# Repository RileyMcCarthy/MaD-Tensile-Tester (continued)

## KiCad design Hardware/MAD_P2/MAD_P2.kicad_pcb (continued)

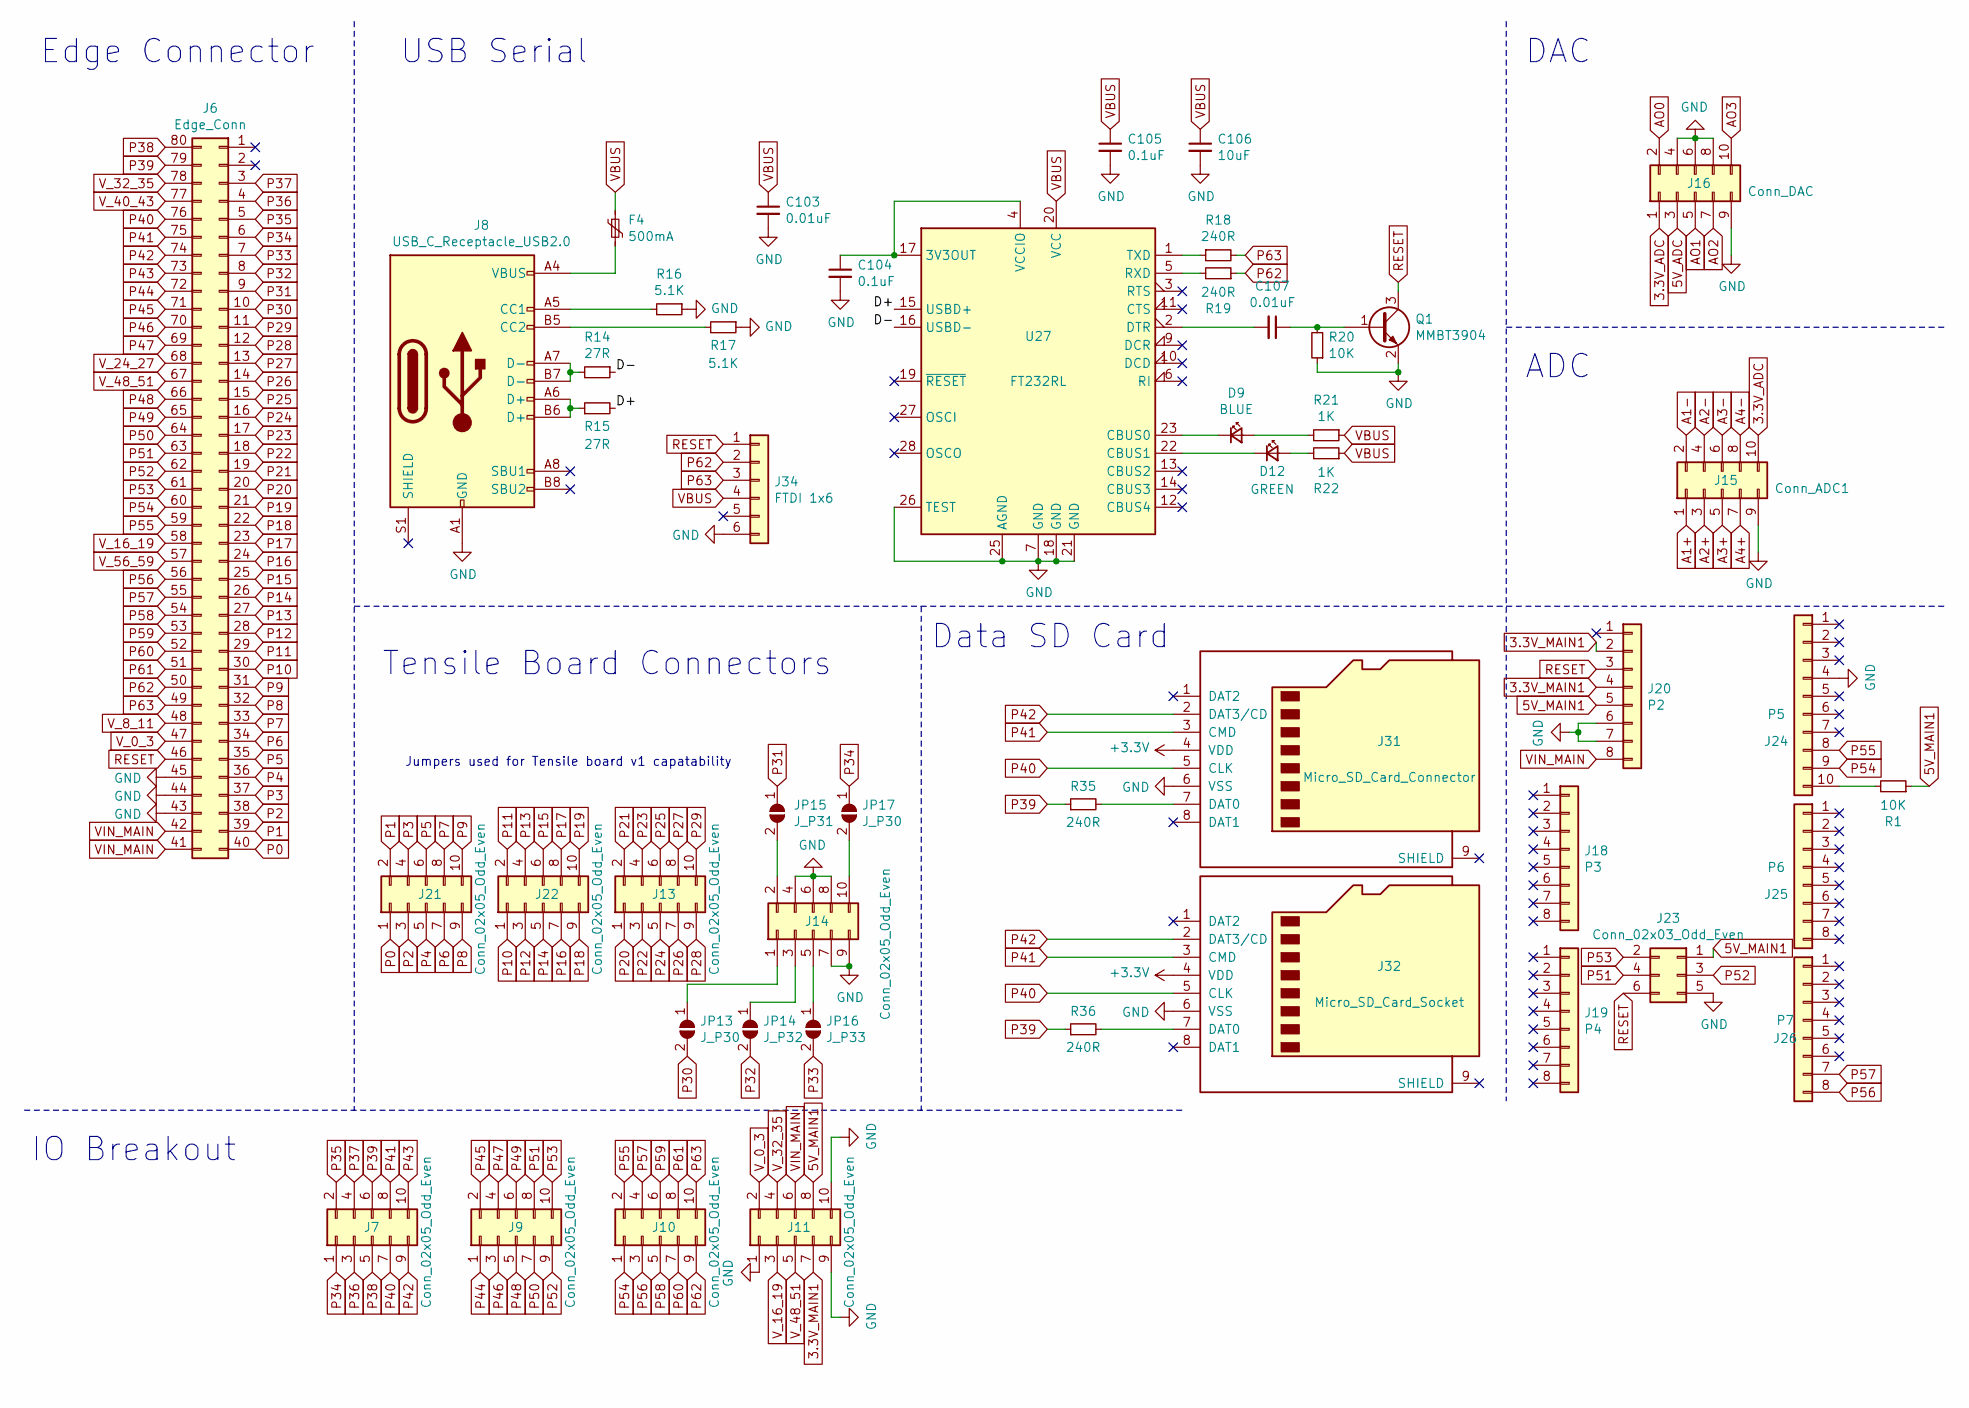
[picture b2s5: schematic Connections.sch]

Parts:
C103, C107: 0.01uF; C_0603_1608Metric; LCSC C57112
C104, C105: 0.1uF; C_0603_1608Metric; LCSC C14663
C106: 10uF; C_0805_2012Metric; LCSC C15850
D9: BLUE; LED_0603_1608Metric; LCSC C72041
D12: GREEN; LED_0603_1608Metric; LCSC C72043
F4: 500mA; Fuse_0603_1608Metric; LCSC C261937
J6: Edge_Conn; P2_Edge_Conn
J7, J9, J10, J11, J13, J14, J21, J22: Conn_02x05_Odd_Even; IDC-Header_2x05_P2.54mm_Vertical; LCSC C5665
J8: USB_C_Receptacle_USB2.0; USB_C_Receptacle_Palconn_UTC16-G; LCSC C393939
J15: Conn_ADC1; IDC-Header_2x05_P2.54mm_Vertical; DIGIKEY S9169-ND
J16: Conn_DAC; IDC-Header_2x05_P2.54mm_Vertical; DIGIKEY S9169-ND
J18: P3; PinSocket_1x08_P2.54mm_Vertical; LCSC C27438
J19: P4; PinSocket_1x08_P2.54mm_Vertical; LCSC C27438
J20: P2; PinSocket_1x08_P2.54mm_Vertical; LCSC C27438
J23: Conn_02x03_Odd_Even; PinSocket_2x03_P2.54mm_Vertical; LCSC C92272
J24: P5; PinSocket_1x10_P2.54mm_Vertical; LCSC C35445
J25: P6; PinSocket_1x08_P2.54mm_Vertical; LCSC C27438
J26: P7; PinSocket_1x08_P2.54mm_Vertical; LCSC C27438
J31: Micro_SD_Card_Connector; WM26501; DIGIKEY WM26501
J32: Micro_SD_Card_Socket; microSD_HC_Hirose_DM3D-SF; DIGIKEY 732-3820-2-ND
J34: FTDI 1x6; PinHeader_1x06_P2.54mm_Vertical
JP13, JP17: J_P30; SolderJumper-2_P1.3mm_Open_Pad1.0x1.5mm
JP14: J_P32; SolderJumper-2_P1.3mm_Open_Pad1.0x1.5mm
JP15: J_P31; SolderJumper-2_P1.3mm_Open_Pad1.0x1.5mm
JP16: J_P33; SolderJumper-2_P1.3mm_Open_Pad1.0x1.5mm
Q1: MMBT3904; SOT-23; LCSC C20526
R1, R20: 10K; R_0603_1608Metric; LCSC C25804
R14, R15: 27R; R_0603_1608Metric; LCSC C25190
R16, R17: 5.1K; R_0603_1608Metric; LCSC C23186
R18, R19, R35, R36: 240R; R_0603_1608Metric; LCSC C23350
R21, R22: 1K; R_0603_1608Metric; LCSC C21190
U27: FT232RL; SSOP-28_5.3x10.2mm_P0.65mm; LCSC C8690

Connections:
3.3V_ADC: J15.10, J16.1; also elsewhere on the board
3.3V_MAIN1: J11.7, J20.2, J20.4; also elsewhere on the board
5V_ADC: J16.3; also elsewhere on the board
5V_MAIN1: J11.8, J20.5, J23.1, R1.1; also elsewhere on the board
+3V3: J31.4 (VDD), J32.4 (VDD); also elsewhere on the board
/Connections/D+: R15.2, U27.15 (USBD+)
/Connections/D-: R14.1, U27.16 (USBD-)
A1+: J15.1; also elsewhere on the board
A1-: J15.2; also elsewhere on the board
A2+: J15.3; also elsewhere on the board
A2-: J15.4; also elsewhere on the board
A3+: J15.5; also elsewhere on the board
A3-: J15.6; also elsewhere on the board
A4+: J15.7; also elsewhere on the board
A4-: J15.8; also elsewhere on the board
AO0: J16.2; also elsewhere on the board
AO1: J16.5; also elsewhere on the board
AO2: J16.7; also elsewhere on the board
AO3: J16.10; also elsewhere on the board
GND: C103.2, C104.2, C105.2, C106.2, J6.43, J6.44, J6.45, J8.A1 (GND), J8.A12 (GND), J8.B1 (GND), J8.B12 (GND), J11.1, J11.9, J11.10, J14.4, J14.6, J14.7, J14.8, J14.9, J15.9, J16.4, J16.6, J16.8, J16.9, J20.6, J20.7, J23.5, J24.4, J31.6 (VSS), J32.6 (VSS), J34.6, Q1.2 (E), R16.1, R17.1, R20.1, U27.7 (GND), U27.18 (GND), U27.21 (GND), U27.25 (AGND), U27.26 (TEST); also elsewhere on the board
unnamed: C104.1, U27.4 (VCCIO), U27.17 (3V3OUT)
unnamed: C107.1, Q1.1 (B), R20.2
unnamed: C107.2, U27.2 (DTR)
unnamed: D9.1 (K), U27.23 (CBUS0)
unnamed: D9.2 (A), R21.2
unnamed: D12.1 (K), U27.22 (CBUS1)
unnamed: D12.2 (A), R22.2
unnamed: F4.2, J8.A4 (VBUS), J8.A9 (VBUS), J8.B4 (VBUS), J8.B9 (VBUS)
unnamed: J8.A5 (CC1), R16.2
unnamed: J8.A6 (D+), J8.B6 (D+), R15.1
unnamed: J8.A7 (D-), J8.B7 (D-), R14.2
unnamed: J8.B5 (CC2), R17.2
unnamed: J14.1, JP13.1 (A)
unnamed: J14.2, JP15.2 (B)
unnamed: J14.3, JP14.1 (A)
unnamed: J14.5, JP16.1 (A)
unnamed: J14.10, JP17.2 (B)
unnamed: J24.10, R1.2
unnamed: J31.7 (DAT0), R35.2
unnamed: J32.7 (DAT0), R36.2
unnamed: R18.1, U27.1 (TXD)
unnamed: R19.2, U27.5 (RXD)
P0: J6.40, J21.1; also elsewhere on the board
P1: J6.39, J21.2; also elsewhere on the board
P2: J6.38, J21.3; also elsewhere on the board
P3: J6.37, J21.4; also elsewhere on the board
P4: J6.36, J21.5; also elsewhere on the board
P5: J6.35, J21.6; also elsewhere on the board
P6: J6.34, J21.7; also elsewhere on the board
P7: J6.33, J21.8; also elsewhere on the board
P8: J6.32, J21.9; also elsewhere on the board
P9: J6.31, J21.10; also elsewhere on the board
P10: J6.30, J22.1; also elsewhere on the board
P11: J6.29, J22.2; also elsewhere on the board
P12: J6.28, J22.3; also elsewhere on the board
P13: J6.27, J22.4; also elsewhere on the board
P14: J6.26, J22.5; also elsewhere on the board
P15: J6.25, J22.6; also elsewhere on the board
P16: J6.24, J22.7; also elsewhere on the board
P17: J6.23, J22.8; also elsewhere on the board
P18: J6.22, J22.9; also elsewhere on the board
P19: J6.21, J22.10; also elsewhere on the board
P20: J6.20, J13.1; also elsewhere on the board
P21: J6.19, J13.2; also elsewhere on the board
P22: J6.18, J13.3; also elsewhere on the board
P23: J6.17, J13.4; also elsewhere on the board
P24: J6.16, J13.5; also elsewhere on the board
P25: J6.15, J13.6; also elsewhere on the board
P26: J6.14, J13.7; also elsewhere on the board
P27: J6.13, J13.8; also elsewhere on the board
P28: J6.12, J13.9; also elsewhere on the board
P29: J6.11, J13.10; also elsewhere on the board
P30: J6.10, JP13.2 (B); also elsewhere on the board
P31: J6.9, JP15.1 (A); also elsewhere on the board
P32: J6.8, JP14.2 (B); also elsewhere on the board
P33: J6.7, JP16.2 (B); also elsewhere on the board
P34: J6.6, J7.1, JP17.1 (A); also elsewhere on the board
P35: J6.5, J7.2; also elsewhere on the board
P36: J6.4, J7.3; also elsewhere on the board
P37: J6.3, J7.4; also elsewhere on the board
P38: J6.80, J7.5; also elsewhere on the board
P39: J6.79, J7.6, R35.1, R36.1; also elsewhere on the board
P40: J6.76, J7.7, J31.5 (CLK), J32.5 (CLK); also elsewhere on the board
P41: J6.75, J7.8, J31.3 (CMD), J32.3 (CMD); also elsewhere on the board
P42: J6.74, J7.9, J31.2 (DAT3/CD), J32.2 (DAT3/CD); also elsewhere on the board
P43: J6.73, J7.10; also elsewhere on the board
P44: J6.72, J9.1; also elsewhere on the board
P45: J6.71, J9.2; also elsewhere on the board
P46: J6.70, J9.3; also elsewhere on the board
P47: J6.69, J9.4; also elsewhere on the board
P48: J6.66, J9.5; also elsewhere on the board
P49: J6.65, J9.6; also elsewhere on the board
P50: J6.64, J9.7; also elsewhere on the board
P51: J6.63, J9.8, J23.4; also elsewhere on the board
P52: J6.62, J9.9, J23.3; also elsewhere on the board
P53: J6.61, J9.10, J23.2; also elsewhere on the board
P54: J6.60, J10.1, J24.9; also elsewhere on the board
P55: J6.59, J10.2, J24.8; also elsewhere on the board
P56: J6.56, J10.3, J26.8; also elsewhere on the board
P57: J6.55, J10.4, J26.7; also elsewhere on the board
P58: J6.54, J10.5; also elsewhere on the board
P59: J6.53, J10.6; also elsewhere on the board
P60: J6.52, J10.7; also elsewhere on the board
P61: J6.51, J10.8; also elsewhere on the board
P62: J6.50, J10.9, J34.2, R19.1; also elsewhere on the board
P63: J6.49, J10.10, J34.3, R18.2; also elsewhere on the board
RESET: J6.46, J20.3, J23.6, J34.1, Q1.3 (C); also elsewhere on the board
VBUS: C103.1, C105.1, C106.1, F4.1, J34.4, R21.1, R22.1, U27.20 (VCC); also elsewhere on the board
VIN_L1: J6.41, J6.42, J11.6, J20.8; also elsewhere on the board
V_0_3: J6.47, J6.48, J6.58, J6.68, J11.2, J11.3; also elsewhere on the board
V_32_35: J6.57, J6.67, J6.77, J6.78, J11.4, J11.5; also elsewhere on the board

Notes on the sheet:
USB Serial
IO Breakout
Edge Connector
Tensile Board Connectors
Jumpers used for Tensile board v1 capatability
DAC
ADC
Data SD Card

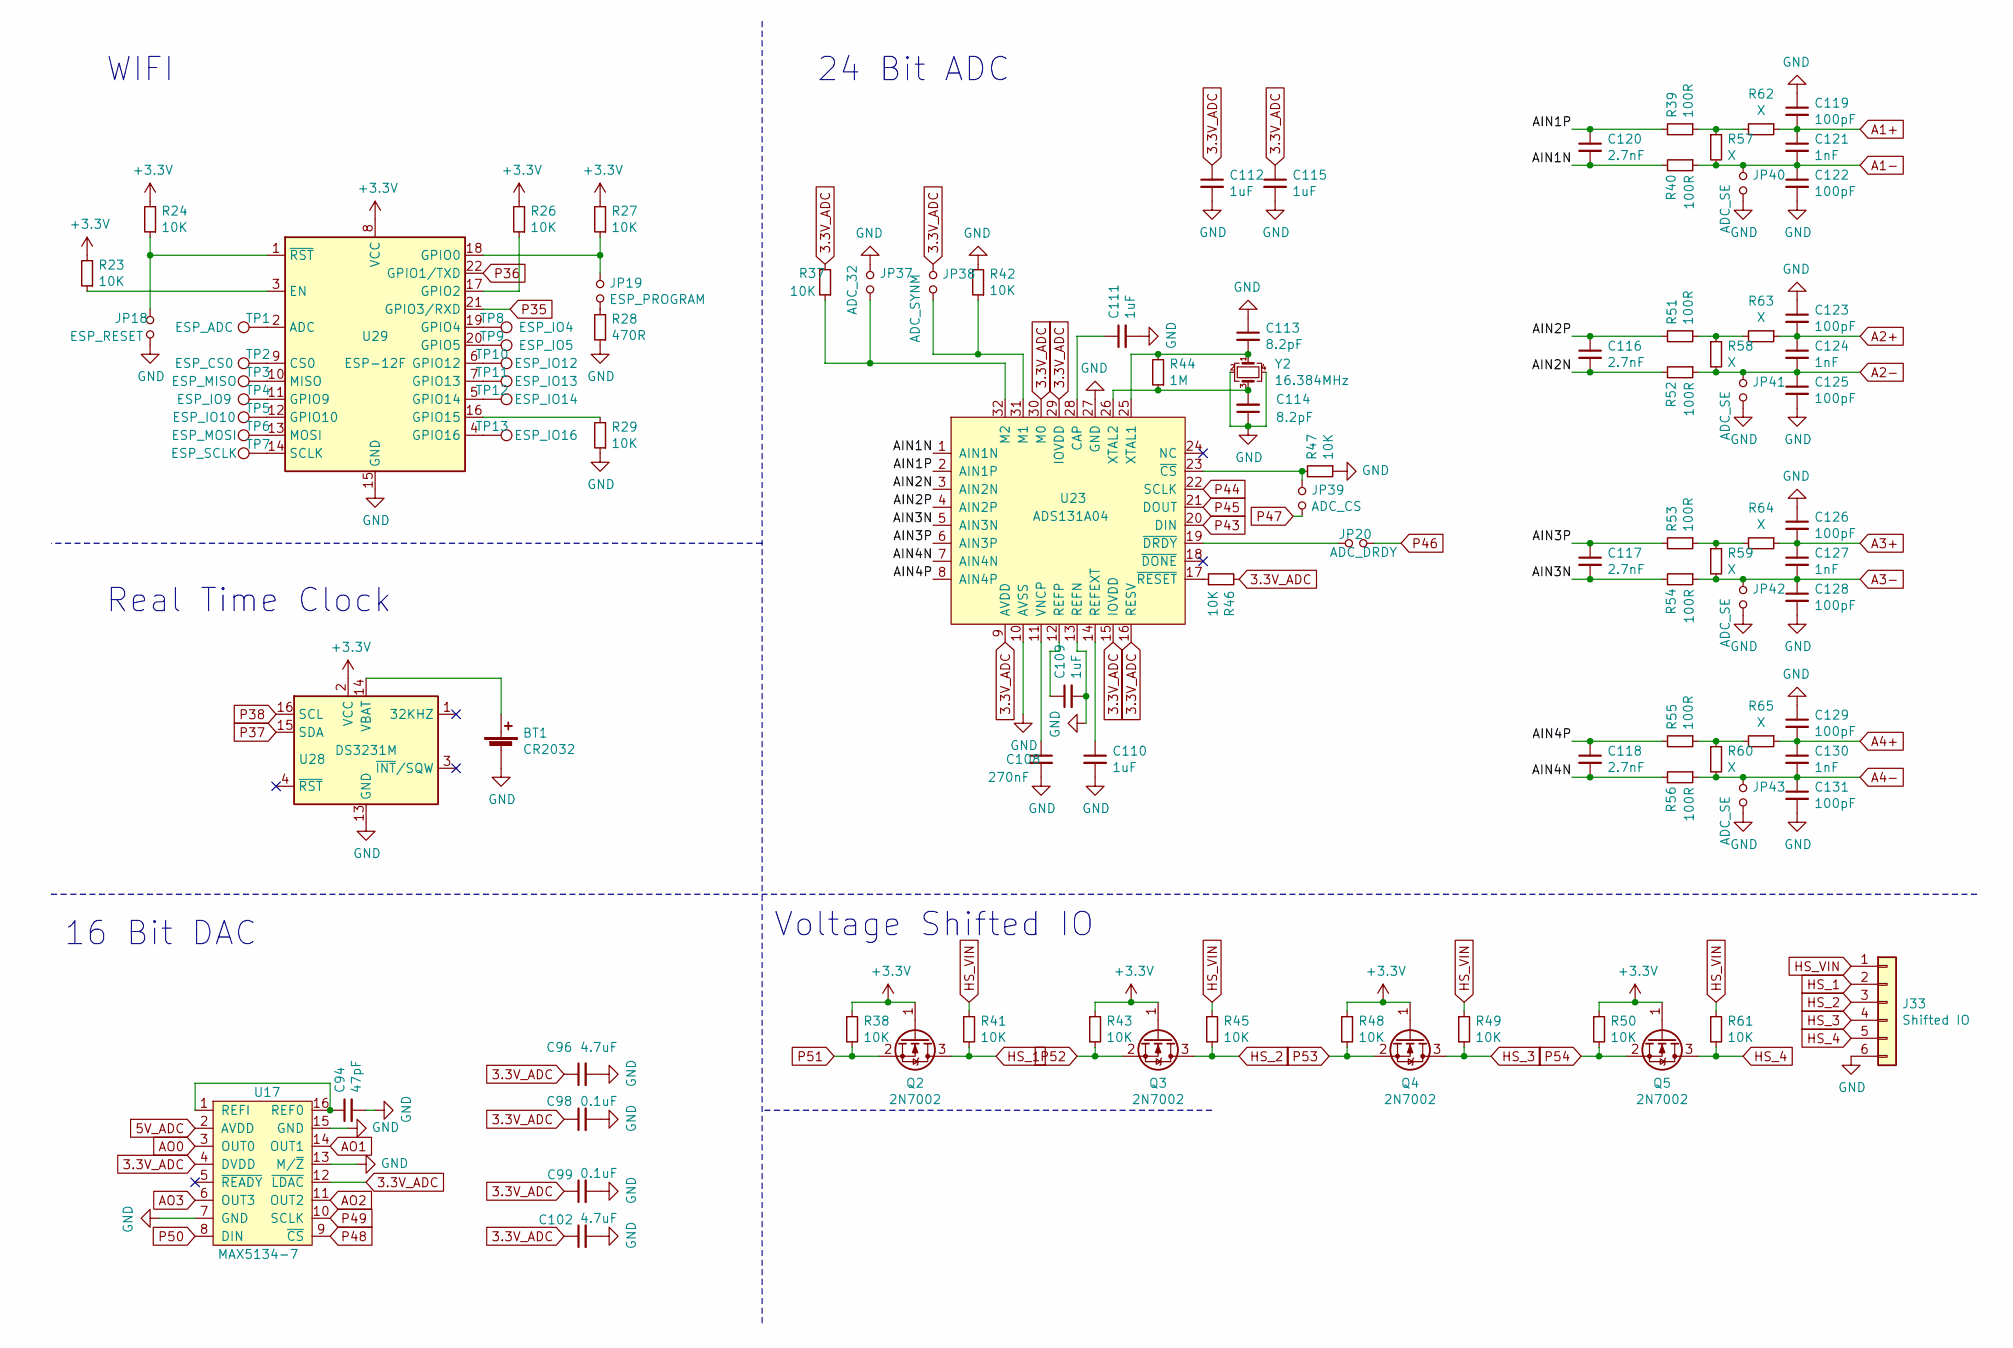
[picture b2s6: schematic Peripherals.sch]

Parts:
BT1: CR2032; BatteryHolder_Keystone_1058_1x2032; LCSC C70377
C94: 47pF; C_0603_1608Metric; LCSC C1671
C96, C102: 4.7uF; C_0603_1608Metric; LCSC C19666
C98, C99: 0.1uF; C_0603_1608Metric; LCSC C14663
C108: 270nF; C_0603_1608Metric; LCSC C376826
C109, C110, C111, C112, C115: 1uF; C_0603_1608Metric; LCSC C15849
C113, C114: 8.2pF; C_0603_1608Metric; LCSC C170126
C116, C117, C118, C120: 2.7nF; C_0603_1608Metric; LCSC C1609
C119, C122, C123, C125, C126, C128, C129, C131: 100pF; C_0603_1608Metric; LCSC C14858
C121, C124, C127, C130: 1nF; C_0603_1608Metric; LCSC C1588
J33: Shifted IO; PinSocket_1x06_P2.54mm_Vertical
JP18: ESP_RESET; SolderJumper-2_P1.3mm_Open_Pad1.0x1.5mm
JP19: ESP_PROGRAM; SolderJumper-2_P1.3mm_Open_Pad1.0x1.5mm
JP20: ADC_DRDY; SolderJumper-2_P1.3mm_Open_Pad1.0x1.5mm
JP37: ADC_32; SolderJumper-2_P1.3mm_Open_Pad1.0x1.5mm
JP38: ADC_SYNM; SolderJumper-2_P1.3mm_Open_Pad1.0x1.5mm
JP39: ADC_CS; SolderJumper-2_P1.3mm_Open_Pad1.0x1.5mm
JP40, JP41, JP42, JP43: ADC_SE; SolderJumper-2_P1.3mm_Open_Pad1.0x1.5mm
Q2, Q3, Q4, Q5: 2N7002; SOT-23; LCSC C8545
R23, R24, R26, R27, R29, R37, R38, R41, R42, R43, R45, R46, R47, R48, R49, R50, R61: 10K; R_0603_1608Metric; LCSC C25804
R28: 470R; R_0603_1608Metric; LCSC C23179
R39, R40, R51, R52, R53, R54, R55, R56: 100R; R_0603_1608Metric; LCSC C22775
R44: 1M; R_0603_1608Metric; LCSC C22935
R57, R58, R59, R60, R62, R63, R64, R65: X; R_0805_2012Metric
TP1: ESP_ADC; TestPoint_Pad_1.0x1.0mm
TP2: ESP_CS0; TestPoint_Pad_1.0x1.0mm
TP3: ESP_MISO; TestPoint_Pad_1.0x1.0mm
TP4: ESP_IO9; TestPoint_Pad_1.0x1.0mm
TP5: ESP_IO10; TestPoint_Pad_1.0x1.0mm
TP6: ESP_MOSI; TestPoint_Pad_1.0x1.0mm
TP7: ESP_SCLK; TestPoint_Pad_1.0x1.0mm
TP8: ESP_IO4; TestPoint_Pad_1.0x1.0mm
TP9: ESP_IO5; TestPoint_Pad_1.0x1.0mm
TP10: ESP_IO12; TestPoint_Pad_1.0x1.0mm
TP11: ESP_IO13; TestPoint_Pad_1.0x1.0mm
TP12: ESP_IO14; TestPoint_Pad_1.0x1.0mm
TP13: ESP_IO16; TestPoint_Pad_1.0x1.0mm
U17: MAX5134-7; TSSOP-16_4.4x5mm_P0.65mm; DIGIKEY MAX5134AGUE
U23: ADS131A04; LQFP-32_5x5mm_P0.5mm; LCSC C882747
U28: DS3231M; SOIC-16W_7.5x10.3mm_P1.27mm; DIGIKEY DS3231M
U29: ESP-12F; ESP-12E; LCSC C82891
Y2: 16.384MHz; Crystal_SMD_3225-4Pin_3.2x2.5mm; LCSC C13739

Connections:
3.3V_ADC: C96.1, C98.1, C99.1, C102.1, C112.1, C115.1, JP38.1, R37.2, R46.2, U17.4 (DVDD), U17.12 (~LDAC), U23.9 (AVDD), U23.15 (IOVDD), U23.16 (RESV), U23.29 (IOVDD), U23.30 (M0); also elsewhere on the board
5V_ADC: U17.2 (AVDD); also elsewhere on the board
+3V3: Q2.1 (G), Q3.1 (G), Q4.1 (G), Q5.1 (G), R23.2, R24.2, R26.2, R27.2, R38.1, R43.1, R48.1, R50.1, U28.2 (VCC), U29.8 (VCC); also elsewhere on the board
/Peripherals/AIN1N: C120.2, R40.2, U23.1 (AIN1N)
/Peripherals/AIN1P: C120.1, R39.2, U23.2 (AIN1P)
/Peripherals/AIN2N: C116.2, R52.2, U23.3 (AIN2N)
/Peripherals/AIN2P: C116.1, R51.2, U23.4 (AIN2P)
/Peripherals/AIN3N: C117.2, R54.2, U23.5 (AIN3N)
/Peripherals/AIN3P: C117.1, R53.2, U23.6 (AIN3P)
/Peripherals/AIN4N: C118.2, R56.2, U23.7 (AIN4N)
/Peripherals/AIN4P: C118.1, R55.2, U23.8 (AIN4P)
A1+: C119.2, C121.1, R62.1; also elsewhere on the board
A1-: C121.2, C122.1, JP40.1, R40.1, R57.2; also elsewhere on the board
A2+: C123.2, C124.1, R63.1; also elsewhere on the board
A2-: C124.2, C125.1, JP41.1, R52.1, R58.2; also elsewhere on the board
A3+: C126.2, C127.1, R64.1; also elsewhere on the board
A3-: C127.2, C128.1, JP42.1, R54.1, R59.2; also elsewhere on the board
A4+: C129.2, C130.1, R65.1; also elsewhere on the board
A4-: C130.2, C131.1, JP43.1, R56.1, R60.2; also elsewhere on the board
AO0: U17.3 (OUT0); also elsewhere on the board
AO1: U17.14 (OUT1); also elsewhere on the board
AO2: U17.11 (OUT2); also elsewhere on the board
AO3: U17.6 (OUT3); also elsewhere on the board
GND: BT1.2 (-), C94.2, C96.2, C98.2, C99.2, C102.2, C108.2, C109.2, C110.2, C111.2, C112.2, C113.1, C114.1, C115.2, C119.1, C122.2, C123.1, C125.2, C126.1, C128.2, C129.1, C131.2, J33.6, JP18.2, JP37.1, JP40.2, JP41.2, JP42.2, JP43.2, R28.1, R29.1, R42.2, R47.1, U17.7 (GND), U17.13 (M/~Z), U17.15 (GND), U23.10 (AVSS), U23.13 (REFN), U23.27 (GND), U28.5 (GND), U28.6 (GND), U28.7 (GND), U28.8 (GND), U28.9 (GND), U28.10 (GND), U28.11 (GND), U28.12 (GND), U28.13 (GND), U29.15 (GND), Y2.2, Y2.4; also elsewhere on the board
HS_1: J33.2, Q2.3 (D), R41.2
HS_2: J33.3, Q3.3 (D), R45.2
HS_3: J33.4, Q4.3 (D), R49.2
HS_4: J33.5, Q5.3 (D), R61.2
HS_VIN: J33.1, R41.1, R45.1, R49.1, R61.1
unnamed: BT1.1 (+), U28.14 (VBAT)
unnamed: C94.1, U17.1 (REFI), U17.16 (REF0)
unnamed: C108.1, U23.11 (VNCP)
unnamed: C109.1, U23.12 (REFP)
unnamed: C110.1, U23.14 (REFEXT)
unnamed: C111.1, U23.28 (CAP)
unnamed: C113.2, R44.2, U23.25 (XTAL1), Y2.1
unnamed: C114.2, R44.1, U23.26 (XTAL2), Y2.3
unnamed: JP18.1, R24.1, U29.1 (~RST)
unnamed: JP19.1, R27.1, U29.18 (GPIO0)
unnamed: JP19.2, R28.2
unnamed: JP20.1, U23.19 (~DRDY)
unnamed: JP37.2, R37.1, U23.32 (M2)
unnamed: JP38.2, R42.1, U23.31 (M1)
unnamed: JP39.1, R47.2, U23.23 (~CS)
unnamed: R23.1, U29.3 (EN)
unnamed: R26.1, U29.17 (GPIO2)
unnamed: R29.2, U29.16 (GPIO15)
unnamed: R39.1, R57.1, R62.2
unnamed: R46.1, U23.17 (~RESET)
unnamed: R51.1, R58.1, R63.2
unnamed: R53.1, R59.1, R64.2
unnamed: R55.1, R60.1, R65.2
unnamed: TP1.1, U29.2 (ADC)
unnamed: TP2.1, U29.9 (CS0)
unnamed: TP3.1, U29.10 (MISO)
unnamed: TP4.1, U29.11 (GPIO9)
unnamed: TP5.1, U29.12 (GPIO10)
unnamed: TP6.1, U29.13 (MOSI)
unnamed: TP7.1, U29.14 (SCLK)
unnamed: TP8.1, U29.19 (GPIO4)
unnamed: TP9.1, U29.20 (GPIO5)
unnamed: TP10.1, U29.6 (GPIO12)
unnamed: TP11.1, U29.7 (GPIO13)
unnamed: TP12.1, U29.5 (GPIO14)
unnamed: TP13.1, U29.4 (GPIO16)
P35: U29.21 (GPIO3/RXD); also elsewhere on the board
P36: U29.22 (GPIO1/TXD); also elsewhere on the board
P37: U28.15 (SDA); also elsewhere on the board
P38: U28.16 (SCL); also elsewhere on the board
P43: U23.20 (DIN); also elsewhere on the board
P44: U23.22 (SCLK); also elsewhere on the board
P45: U23.21 (DOUT); also elsewhere on the board
P46: JP20.2; also elsewhere on the board
P47: JP39.2; also elsewhere on the board
P48: U17.9 (~CS); also elsewhere on the board
P49: U17.10 (SCLK); also elsewhere on the board
P50: U17.8 (DIN); also elsewhere on the board
P51: Q2.2 (S), R38.2; also elsewhere on the board
P52: Q3.2 (S), R43.2; also elsewhere on the board
P53: Q4.2 (S), R48.2; also elsewhere on the board
P54: Q5.2 (S), R50.2; also elsewhere on the board

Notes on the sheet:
WIFI
Real Time Clock
24 Bit ADC
16 Bit DAC
Voltage Shifted IO

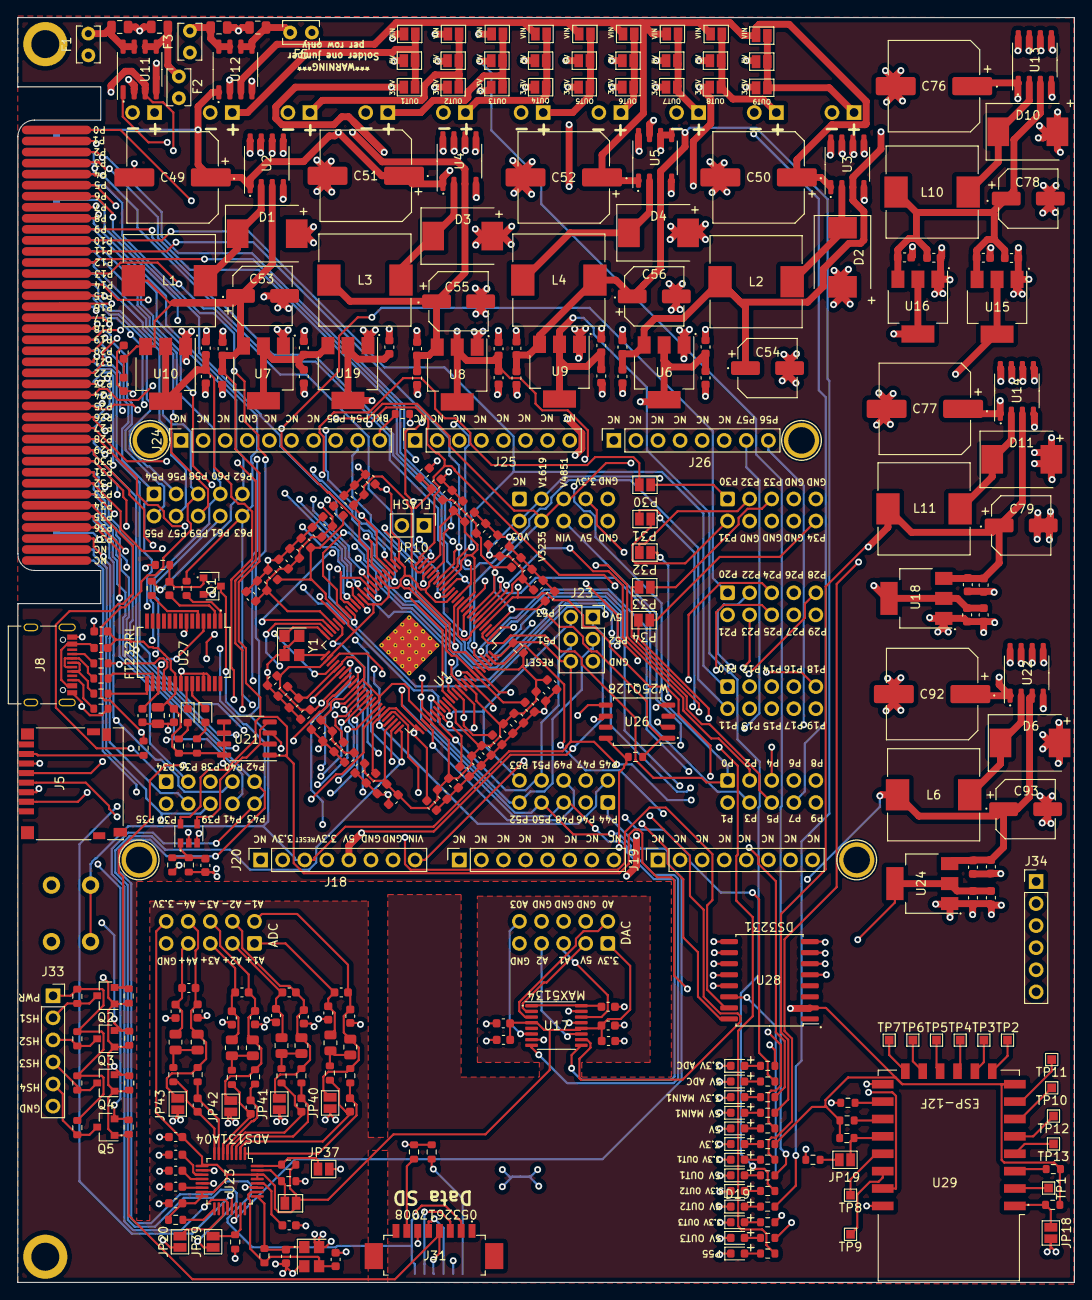
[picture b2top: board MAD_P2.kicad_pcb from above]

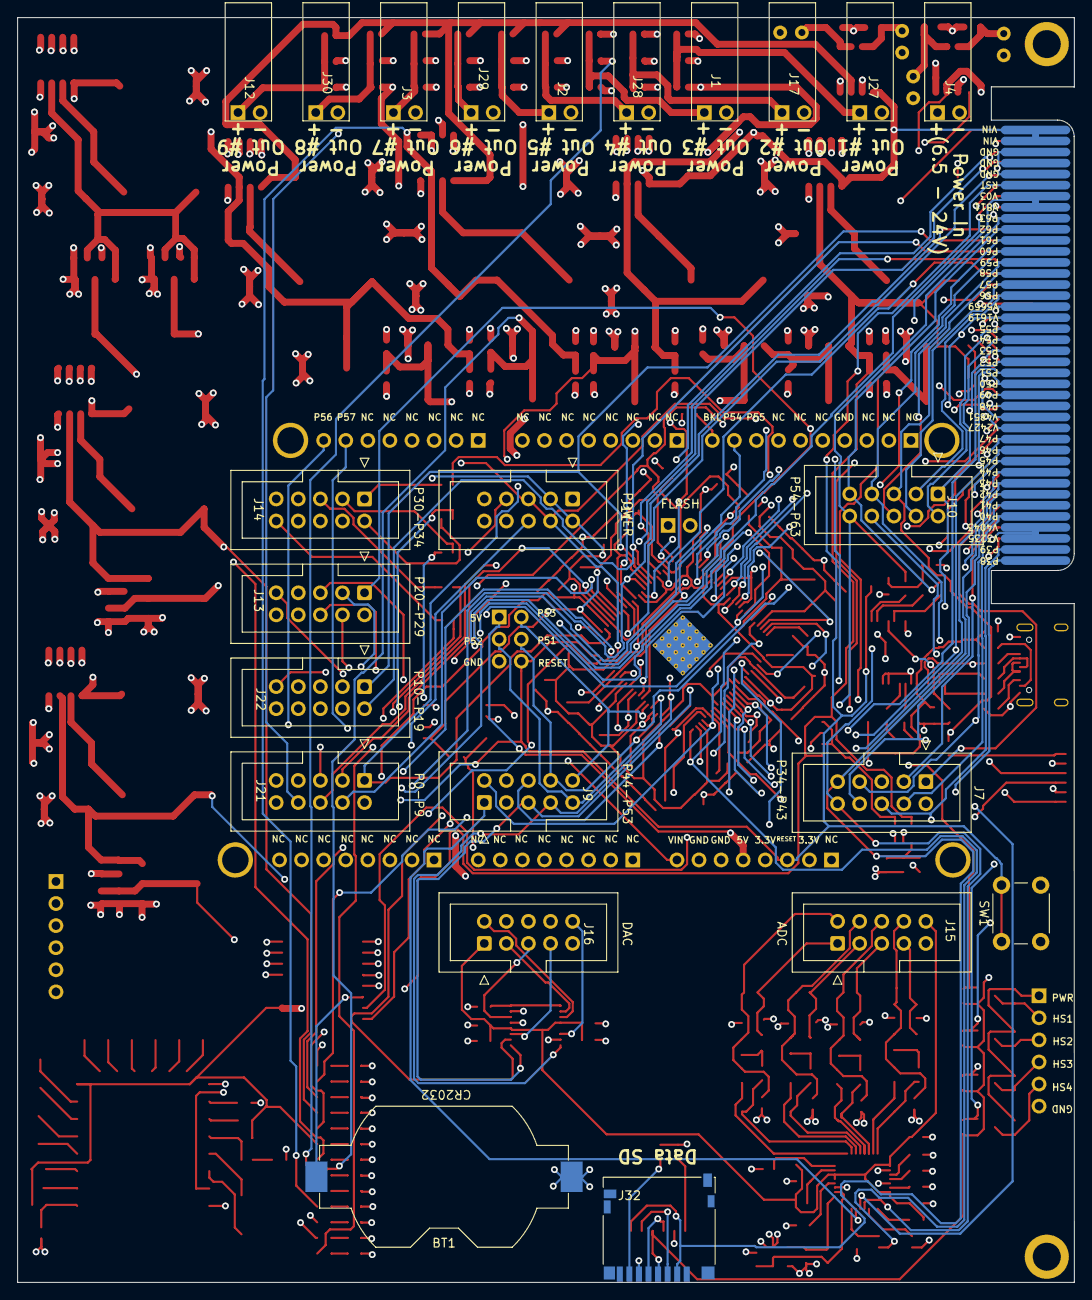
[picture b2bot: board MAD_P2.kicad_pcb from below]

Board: 4 copper layers, 121.6 x 145.5 mm, 366 parts (23 on the bottom side), 213 nets.

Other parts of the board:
DISP_HOLE_1, DISP_HOLE_3: Hole_5.08
P8, P10, P11, P13: CONN_01X01; Arduino_1pin

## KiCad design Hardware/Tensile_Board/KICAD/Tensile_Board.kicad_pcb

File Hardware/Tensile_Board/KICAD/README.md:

# Tensile_Board

# AM26LS32
The datasheet for the DYN4 recommends a AM2632C or equivalent. The difference between the two IC's are the AM26LS32
has around the switching frequency of the AM26C32. This wont be an issue due to the max pulses per revolution 
the incremential encoder library can handle is 3332ppr at 5000RPM.
(https://forums.parallax.com/discussion/89954/quadrature-encodersam26%20l)
At 3332ppr and 5000RPM we get a switching frequency of 277KHz which is well in spec of the AM26LS32(around 20MHz max).

This limits the DYN4 line_num (Section 4.5 in DYN4 manual) which determines the ppm = 4* line_num = 3332. Giving
a line_num = 833.

# 6N137
The optocoupler used for isolation of the encoder lines needs to handle signals switching max 277KHz. The 6N137
can handle up to 20MHz (1/(t_r + t_f)) making it very capable for our speeds.

Next choosing the input resistor of 480ohms. This was determined using the V_f typical of 1.4V, with an input of 5V 
to achieve a forward current of 7.5mA (recommended) we will need a 480ohm resistor.

# Motor IO
The IO to the motor must be completely isolated. For recieving signals from the motor a simple optocoupler with a 
1k resistor is needed(YN4 manual section 2.3.2). To send signals to the motor we will use a line driver (AM26LS31CDR)
and optocoupler. The line driver will allow a high speed signal travel over longer distances to the motor. This setup
will be the reverse setup used to read the DYN4 encoder output.

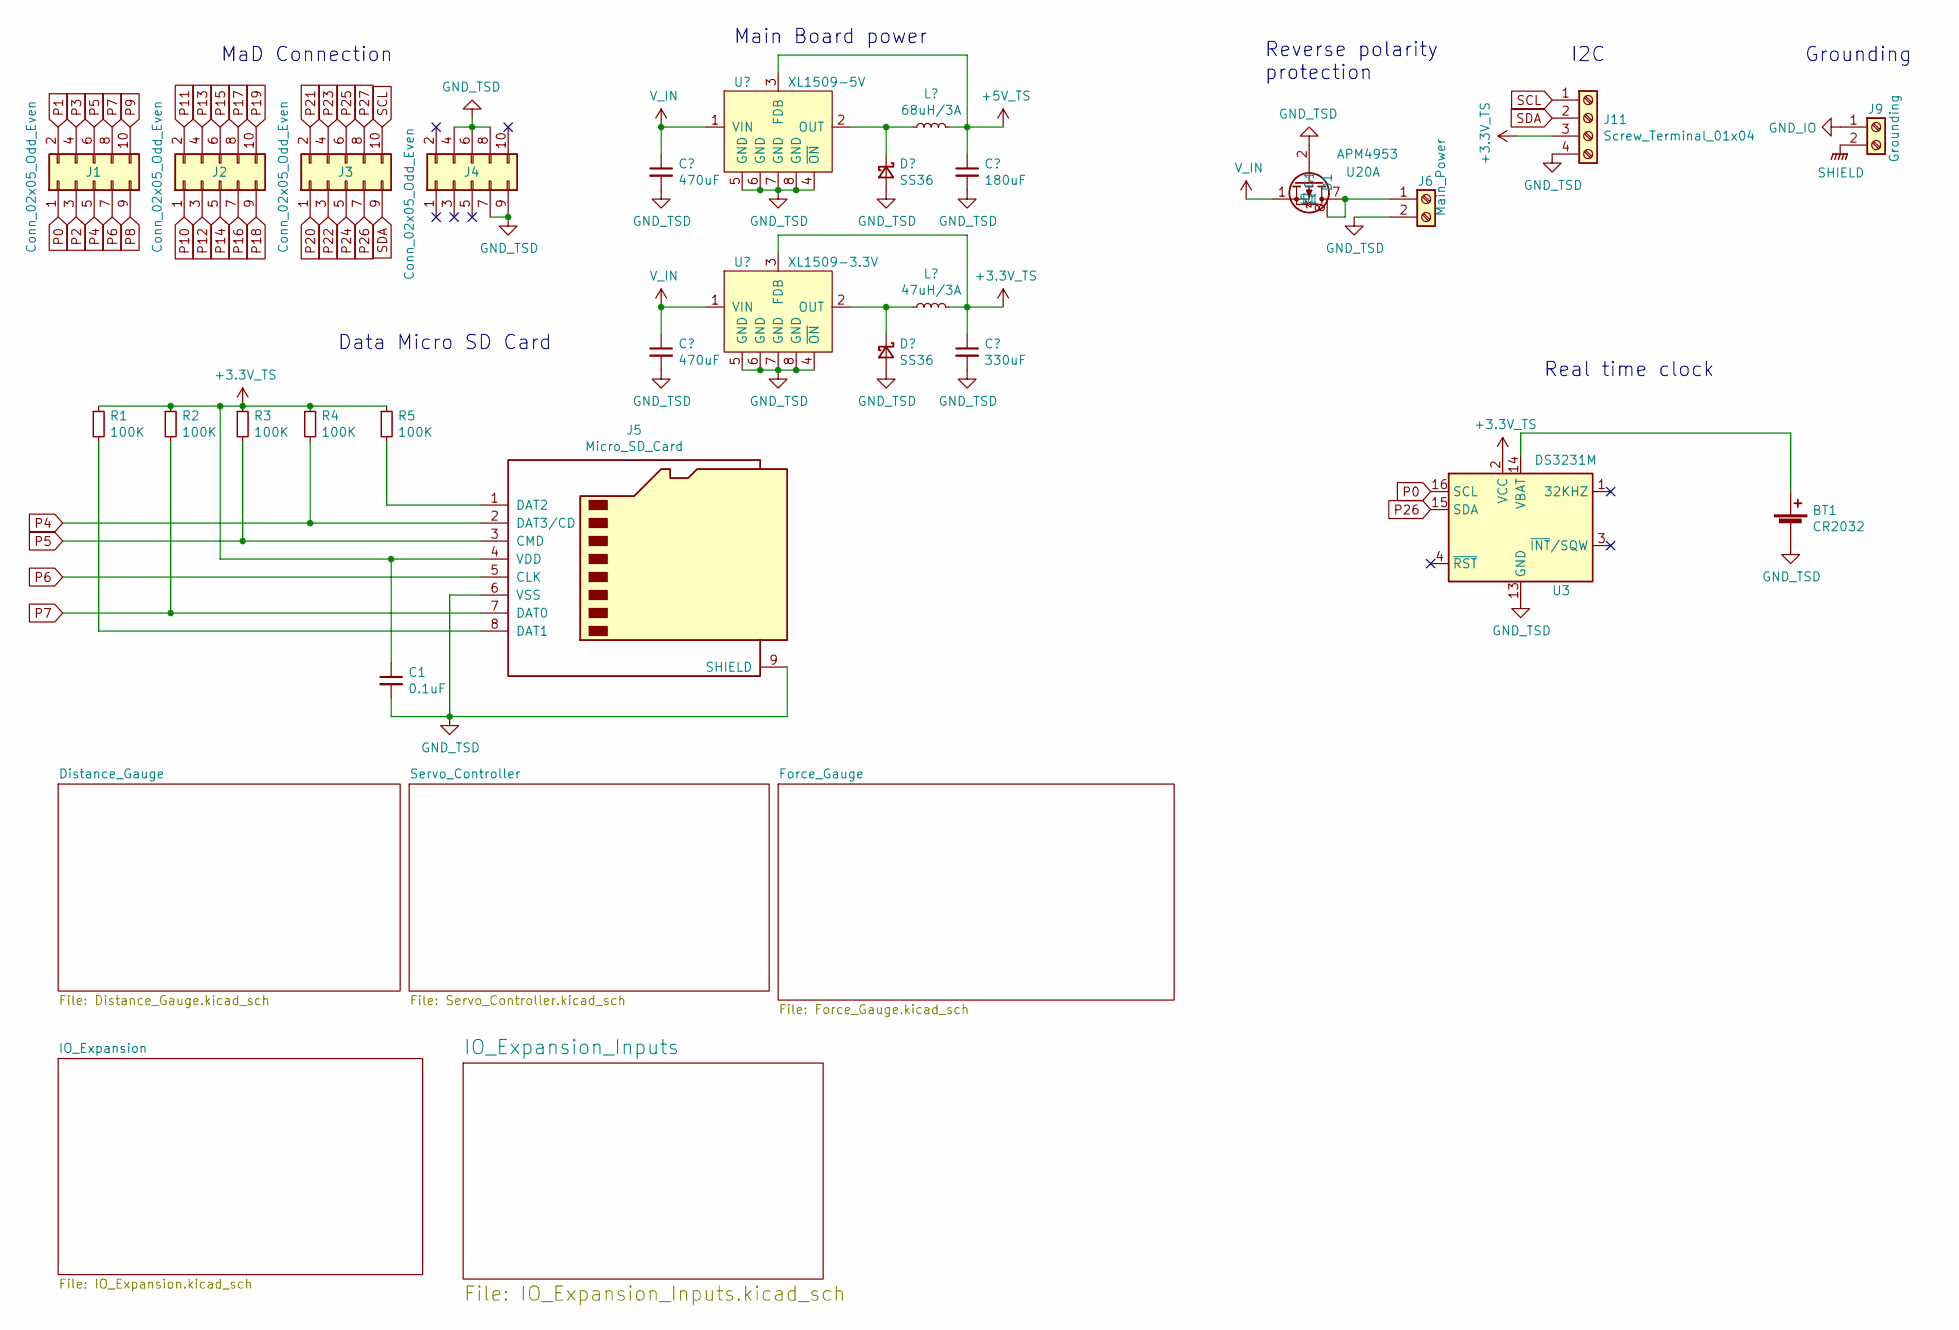
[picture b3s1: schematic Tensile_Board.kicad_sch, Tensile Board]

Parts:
BT1: CR2032; BatteryHolder_Keystone_1058_1x2032; LCSC C70377
C1: 0.1uF; C_0603_1608Metric; LCSC C14663
J1, J2, J3, J4: Conn_02x05_Odd_Even; PinSocket_2x05_P2.54mm_Vertical; LCSC C221045
J5: Micro_SD_Card; WM26501
J6: Main_Power; TerminalBlock_bornier-2_P5.08mm
J9: Grounding; TerminalBlock_bornier-2_P5.08mm
J11: Screw_Terminal_01x04; TerminalBlock_4Ucon_1x04_P3.50mm_Vertical
R1, R2, R3, R4, R5: 100K; R_0603_1608Metric; LCSC C25803
U3: DS3231M; SOIC-16W_7.5x10.3mm_P1.27mm; LCSC C37663
U20: APM4953; SOP-8_3.9x4.9mm_P1.27mm; LCSC C20897

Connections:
GND_IO: J9.1; also elsewhere on the board
GND_TSD: BT1.2 (-), C1.2, J4.4, J4.5, J4.6, J4.7, J4.8, J4.9, J5.6 (VSS), J5.9 (SHIELD), J6.2, J11.4, U3.5 (GND), U3.6 (GND), U3.7 (GND), U3.8 (GND), U3.9 (GND), U3.10 (GND), U3.11 (GND), U3.12 (GND), U3.13 (GND), U20.2 (G1); also elsewhere on the board
unnamed: BT1.1 (+), U3.14 (VBAT)
unnamed: J5.1 (DAT2), R5.2
unnamed: J5.8 (DAT1), R1.2
unnamed: J6.1, U20.7 (D1), U20.8 (D1)
P1: J1.2
P2: J1.3
P3: J1.4
P4: J1.5, J5.2 (DAT3/CD), R4.2
P5: J1.6, J5.3 (CMD), R3.2
P6: J1.7, J5.5 (CLK)
P7: J1.8, J5.7 (DAT0), R2.2
P8: J1.9; also elsewhere on the board
P9: J1.10
P10: J2.1
P11: J2.2; also elsewhere on the board
P12: J2.3; also elsewhere on the board
P13: J2.4; also elsewhere on the board
P14: J2.5; also elsewhere on the board
P15: J2.6; also elsewhere on the board
P16: J2.7; also elsewhere on the board
P17: J2.8; also elsewhere on the board
P18: J2.9
P19: J2.10; also elsewhere on the board
P20: J3.1; also elsewhere on the board
P21: J3.2; also elsewhere on the board
P22: J3.3
P23: J3.4
P24: J3.5
P25: J3.6
P27: J3.8
SCL: J3.10, J11.1
SDA: J3.9, J11.2
SHIELD: J9.2; also elsewhere on the board
V_IN: U20.1 (S1); also elsewhere on the board

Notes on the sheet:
Grounding
I2C
Main Board power
Data Micro SD Card
MaD Connection
Real time clock
Reverse polarity protection
